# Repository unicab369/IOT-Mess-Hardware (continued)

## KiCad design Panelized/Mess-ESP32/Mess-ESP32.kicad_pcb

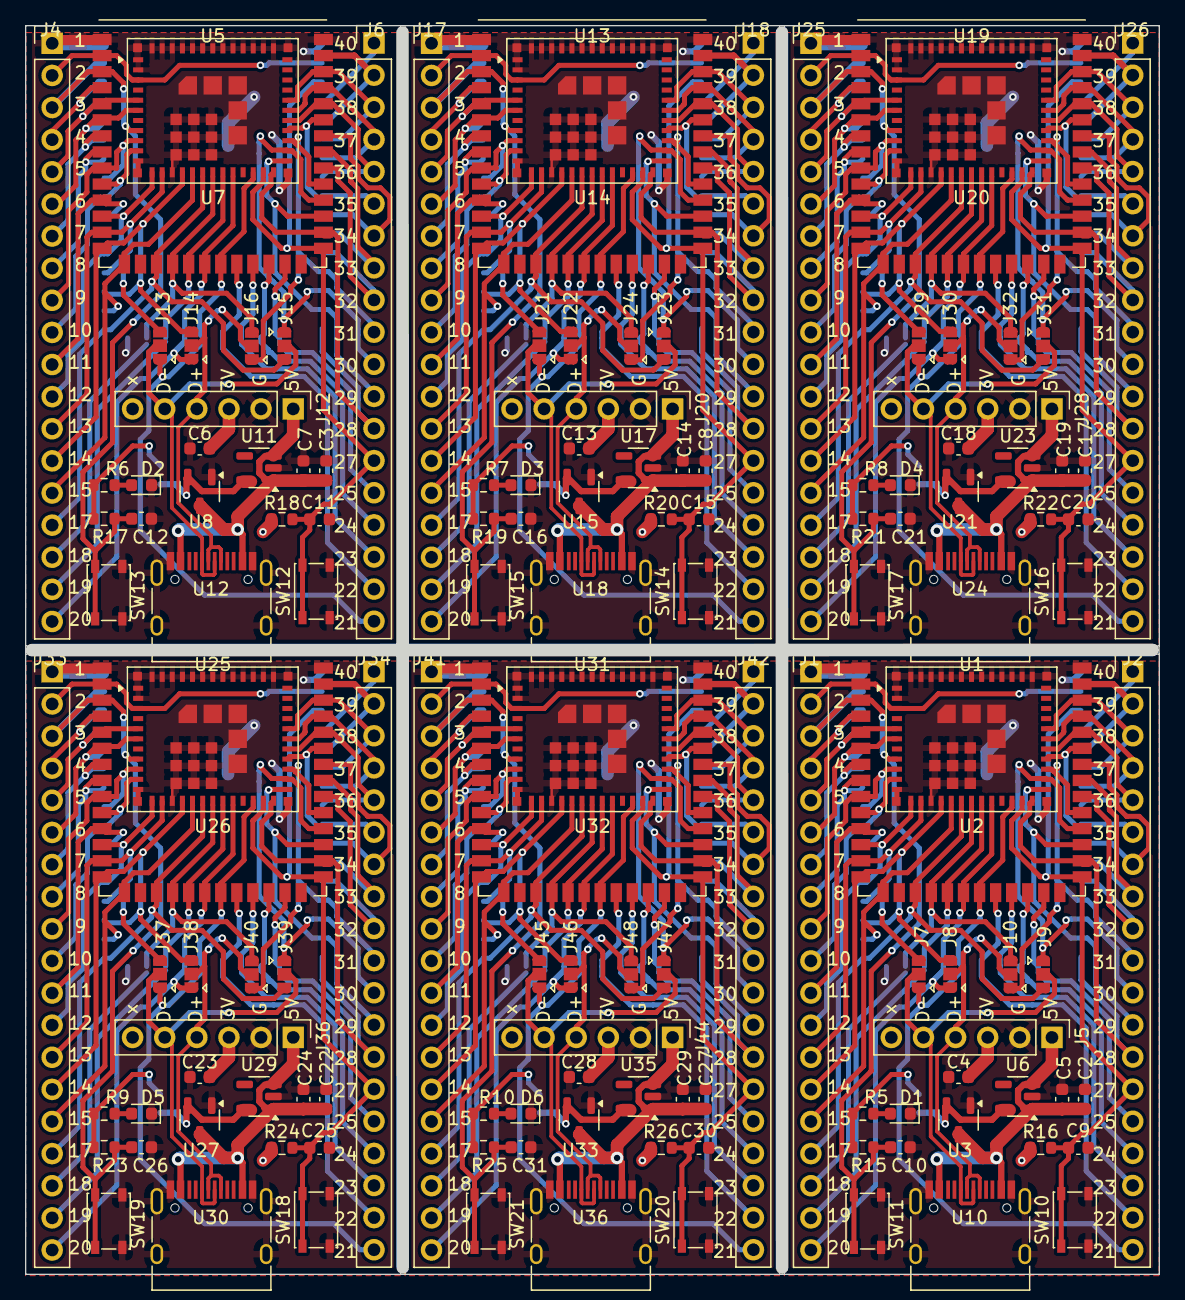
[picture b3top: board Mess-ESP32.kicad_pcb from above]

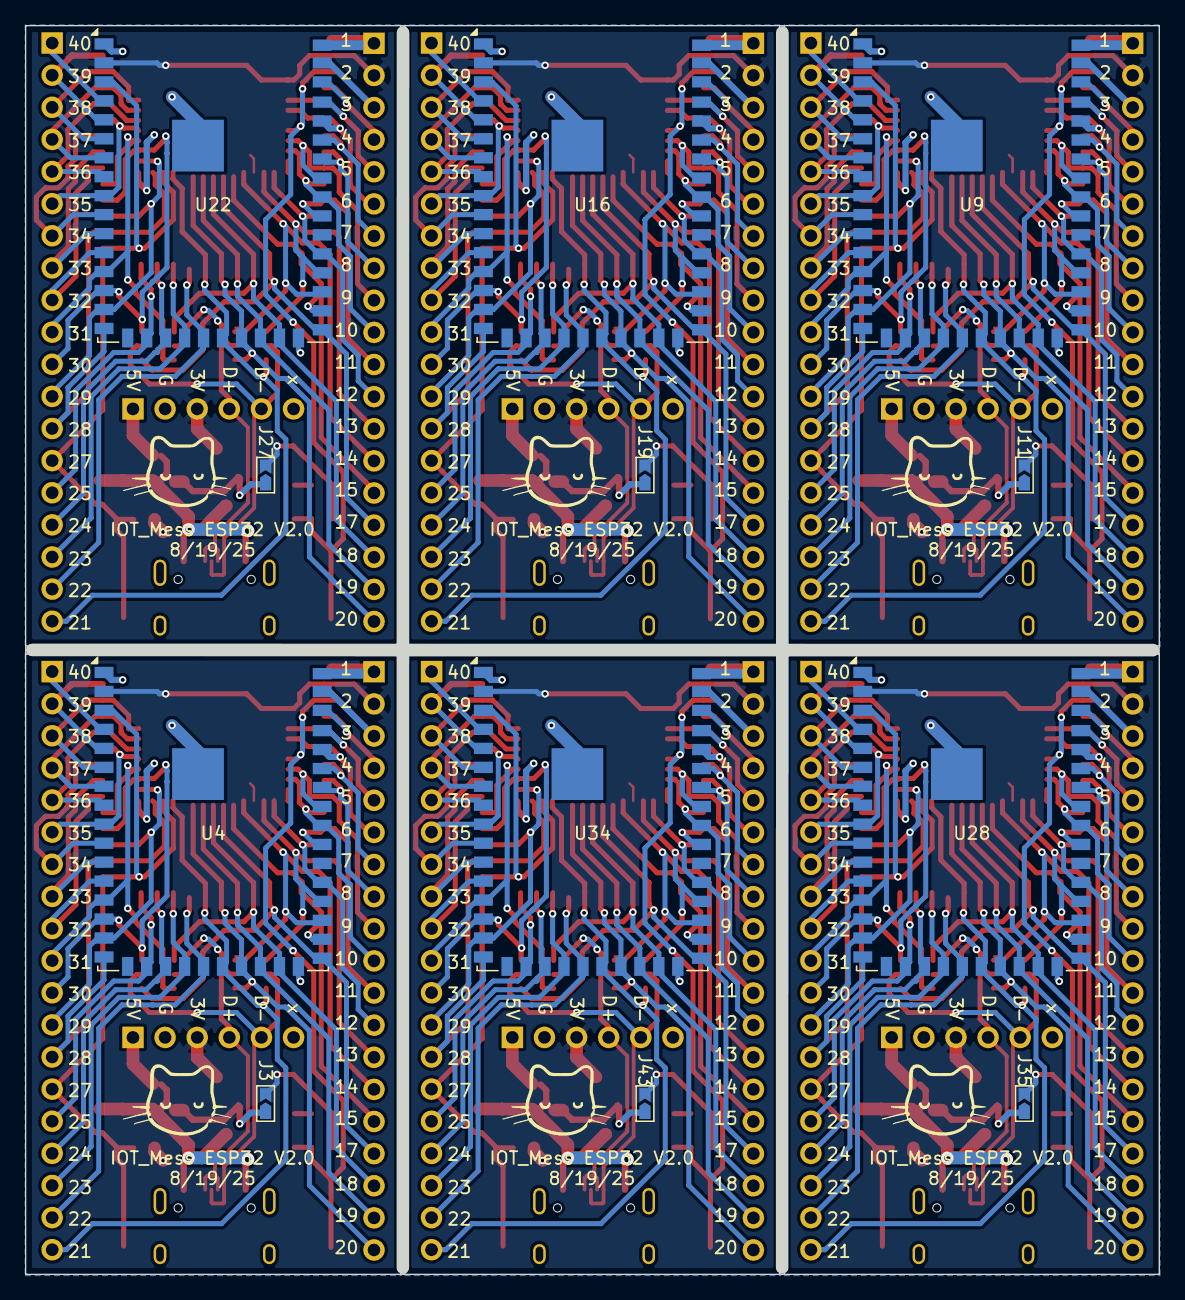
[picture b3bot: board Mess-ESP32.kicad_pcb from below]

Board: 2 copper layers, 89.7 x 98.8 mm, 150 parts (12 on the bottom side), 43 nets.

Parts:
C2, C3, C8, C17, C22, C27: 10u; C_0603_1608Metric
C4, C5, C6, C7, C13, C14, C18, C19, C23, C24, C28, C29: 1u; C_0603_1608Metric
C9, C10, C11, C12, C15, C16, C20, C21, C25, C26, C30, C31: .1u; C_0603_1608Metric
D1, D2, D3, D4, D5, D6: LED; LED_0603_1608Metric
J1, J2, J4, J6, J17, J18, J25, J26, J33, J34, J41, J42: Conn_01x19_Pin; PinHeader_1x19_P2.54mm_Vertical
J3, J11, J19, J27, J35, J43: Jumper_2; Jumpper-triangle
J5, J12, J20, J28, J36, J44: Conn_01x06_Pin; PinHeader_1x06_P2.54mm_Vertical
J7, J8, J9, J10, J13, J14, J15, J16, J21, J22, J23, J24, J29, J30, J31, J32, J37, J38, J39, J40, J45, J46, J47, J48: Jumper; Jumper-3_P1.3mm_Open_RoundedPad1.0x1.5mm
R5, R6, R7, R8, R9, R10: R; R_0603_1608Metric
R15, R16, R17, R18, R19, R20, R21, R22, R23, R24, R25, R26: 10K; R_0603_1608Metric
SW10, SW11, SW12, SW13, SW14, SW15, SW16, SW17, SW18, SW19, SW20, SW21: SW_Push; SW_SPST_PTS810
U1, U5, U13, U19, U25, U31: ESP32-S3-WROOM-1
U2, U7, U14, U20, U26, U32: ESP32-C6-MINI-1
U3, U8, U15, U21, U27, U33: XC6206PxxxMR; SOT-23-3
U4, U9, U16, U22, U28, U34: ESP32-S2-WROVER
U6, U11, U17, U23, U29, U35: ME6211C33M5; SOT-23-5
U10, U12, U18, U24, U30, U36: USB_C_Receptacle_USB2.0_16P; USB_C_Receptacle_HRO_TYPE-C-31-M-12

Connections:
5V: C2.1, C3.1, C5.1, C7.1, C8.1, C14.1, C17.1, C19.1, C22.1, C24.1, C27.1, C29.1, J5.1, J12.1, J20.1, J28.1, J36.1, J44.1, U3.3 (VI), U6.1 (V_{IN}), U6.3 (CE), U8.3 (VI), U10.A4 (VBUS), U10.A9 (VBUS), U10.B4 (VBUS), U10.B9 (VBUS), U11.1 (V_{IN}), U11.3 (CE), U12.A4 (VBUS), U12.A9 (VBUS), U12.B4 (VBUS), U12.B9 (VBUS), U15.3 (VI), U17.1 (V_{IN}), U17.3 (CE), U18.A4 (VBUS), U18.A9 (VBUS), U18.B4 (VBUS), U18.B9 (VBUS), U21.3 (VI), U23.1 (V_{IN}), U23.3 (CE), U24.A4 (VBUS), U24.A9 (VBUS), U24.B4 (VBUS), U24.B9 (VBUS), U27.3 (VI), U29.1 (V_{IN}), U29.3 (CE), U30.A4 (VBUS), U30.A9 (VBUS), U30.B4 (VBUS), U30.B9 (VBUS), U33.3 (VI), U35.1 (V_{IN}), U35.3 (CE), U36.A4 (VBUS), U36.A9 (VBUS), U36.B4 (VBUS), U36.B9 (VBUS)
BOOT: C9.1, C11.1, C15.1, C20.1, C25.1, C30.1, J2.14, J6.14, J18.14, J26.14, J34.14, J42.14, R16.1, R18.1, R20.1, R22.1, R24.1, R26.1, SW10.1, SW12.1, SW14.1, SW16.1, SW18.1, SW20.1, U1.27 (IO9/IO0), U2.23 (IO9), U4.3 (IO00), U5.27 (IO9/IO0), U7.23 (IO9), U9.3 (IO00), U13.27 (IO9/IO0), U14.23 (IO9), U16.3 (IO00), U19.27 (IO9/IO0), U20.23 (IO9), U22.3 (IO00), U25.27 (IO9/IO0), U26.23 (IO9), U28.3 (IO00), U31.27 (IO9/IO0), U32.23 (IO9), U34.3 (IO00)
D+: J5.4, J8.2 (C), J10.2 (C), J12.4, J14.2 (C), J16.2 (C), J20.4, J22.2 (C), J24.2 (C), J28.4, J30.2 (C), J32.2 (C), J36.4, J38.2 (C), J40.2 (C), J44.4, J46.2 (C), J48.2 (C), U10.A6 (D+), U10.B6 (D+), U12.A6 (D+), U12.B6 (D+), U18.A6 (D+), U18.B6 (D+), U24.A6 (D+), U24.B6 (D+), U30.A6 (D+), U30.B6 (D+), U36.A6 (D+), U36.B6 (D+)
D-: J5.5, J7.2 (C), J9.2 (C), J12.5, J13.2 (C), J15.2 (C), J20.5, J21.2 (C), J23.2 (C), J28.5, J29.2 (C), J31.2 (C), J36.5, J37.2 (C), J39.2 (C), J44.5, J45.2 (C), J47.2 (C), U10.A7 (D-), U10.B7 (D-), U12.A7 (D-), U12.B7 (D-), U18.A7 (D-), U18.B7 (D-), U24.A7 (D-), U24.B7 (D-), U30.A7 (D-), U30.B7 (D-), U36.A7 (D-), U36.B7 (D-)
unnamed: D1.2 (A), D2.2 (A), D3.2 (A), D4.2 (A), D5.2 (A), D6.2 (A), R5.2, R6.2, R7.2, R8.2, R9.2, R10.2
unnamed: J3.1 (A), J11.1 (A), J19.1 (A), J27.1 (A), J35.1 (A), J43.1 (A), U3.2 (VO), U6.5 (V_{OUT}), U8.2 (VO), U11.5 (V_{OUT}), U15.2 (VO), U17.5 (V_{OUT}), U21.2 (VO), U23.5 (V_{OUT}), U27.2 (VO), U29.5 (V_{OUT}), U33.2 (VO), U35.5 (V_{OUT})
P1: C2.2, C3.2, C4.2, C5.2, C6.2, C7.2, C8.2, C9.2, C10.2, C11.2, C12.2, C13.2, C14.2, C15.2, C16.2, C17.2, C18.2, C19.2, C20.2, C21.2, C22.2, C23.2, C24.2, C25.2, C26.2, C27.2, C28.2, C29.2, C30.2, C31.2, D1.1 (K), D2.1 (K), D3.1 (K), D4.1 (K), D5.1 (K), D6.1 (K), J1.1, J4.1, J5.2, J12.2, J17.1, J20.2, J25.1, J28.2, J33.1, J36.2, J41.1, J44.2, SW10.2, SW11.2, SW12.2, SW13.2, SW14.2, SW15.2, SW16.2, SW17.2, SW18.2, SW19.2, SW20.2, SW21.2, U1.1 (GND), U1.40 (GND), U1.41 (GND), U2.1 (GND), U2.2 (GND), U2.11 (GND), U2.14 (GND), U2.36 (GND), U2.37 (GND), U2.38 (GND), U2.39 (GND), U2.40 (GND), U2.41 (GND), U2.42 (GND), U2.43 (GND), U2.44 (GND), U2.45 (GND), U2.46 (GND), U2.47 (GND), U2.48 (GND), U2.49 (GND), U2.50 (GND), U2.51 (GND), U2.52 (GND), U2.53 (GND), U3.1 (GND), U4.1 (GND), U4.26 (GND), U4.42 (GND), U4.43 (GND), U5.1 (GND), U5.40 (GND), U5.41 (GND), U6.2 (V_{SS}), U7.1 (GND), U7.2 (GND), U7.11 (GND), U7.14 (GND), U7.36 (GND), U7.37 (GND), U7.38 (GND), U7.39 (GND), U7.40 (GND), U7.41 (GND), U7.42 (GND), U7.43 (GND), U7.44 (GND), U7.45 (GND), U7.46 (GND), U7.47 (GND), U7.48 (GND), U7.49 (GND), U7.50 (GND), U7.51 (GND), U7.52 (GND), U7.53 (GND), U8.1 (GND), U9.1 (GND), U9.26 (GND), U9.42 (GND), U9.43 (GND), U10.A1 (GND), U10.A12 (GND), U10.B1 (GND), U10.B12 (GND), U10.S1 (SHIELD), U11.2 (V_{SS}), U12.A1 (GND), U12.A12 (GND), U12.B1 (GND), U12.B12 (GND), U12.S1 (SHIELD), U13.1 (GND), U13.40 (GND), U13.41 (GND), U14.1 (GND), U14.2 (GND), U14.11 (GND), U14.14 (GND), U14.36 (GND), U14.37 (GND), U14.38 (GND), U14.39 (GND), U14.40 (GND), U14.41 (GND), U14.42 (GND), U14.43 (GND), U14.44 (GND), U14.45 (GND), U14.46 (GND), U14.47 (GND), U14.48 (GND), U14.49 (GND), U14.50 (GND), U14.51 (GND), U14.52 (GND), U14.53 (GND), U15.1 (GND), U16.1 (GND), U16.26 (GND), U16.42 (GND), U16.43 (GND), U17.2 (V_{SS}), U18.A1 (GND), U18.A12 (GND), U18.B1 (GND), U18.B12 (GND), U18.S1 (SHIELD), U19.1 (GND), U19.40 (GND), U19.41 (GND), U20.1 (GND), U20.2 (GND), U20.11 (GND), U20.14 (GND), U20.36 (GND), U20.37 (GND), U20.38 (GND), U20.39 (GND), U20.40 (GND), U20.41 (GND), U20.42 (GND), U20.43 (GND), U20.44 (GND), U20.45 (GND), U20.46 (GND), U20.47 (GND), U20.48 (GND), U20.49 (GND), U20.50 (GND), U20.51 (GND), U20.52 (GND), U20.53 (GND), U21.1 (GND), U22.1 (GND), U22.26 (GND), U22.42 (GND), U22.43 (GND), U23.2 (V_{SS}), U24.A1 (GND), U24.A12 (GND), U24.B1 (GND), U24.B12 (GND), U24.S1 (SHIELD), U25.1 (GND), U25.40 (GND), U25.41 (GND), U26.1 (GND), U26.2 (GND), U26.11 (GND), U26.14 (GND), U26.36 (GND), U26.37 (GND), U26.38 (GND), U26.39 (GND), U26.40 (GND), U26.41 (GND), U26.42 (GND), U26.43 (GND), U26.44 (GND), U26.45 (GND), U26.46 (GND), U26.47 (GND), U26.48 (GND), U26.49 (GND), U26.50 (GND), U26.51 (GND), U26.52 (GND), U26.53 (GND), U27.1 (GND), U28.1 (GND), U28.26 (GND), U28.42 (GND), U28.43 (GND), U29.2 (V_{SS}), U30.A1 (GND), U30.A12 (GND), U30.B1 (GND), U30.B12 (GND), U30.S1 (SHIELD), U31.1 (GND), U31.40 (GND), U31.41 (GND), U32.1 (GND), U32.2 (GND), U32.11 (GND), U32.14 (GND), U32.36 (GND), U32.37 (GND), U32.38 (GND), U32.39 (GND), U32.40 (GND), U32.41 (GND), U32.42 (GND), U32.43 (GND), U32.44 (GND), U32.45 (GND), U32.46 (GND), U32.47 (GND), U32.48 (GND), U32.49 (GND), U32.50 (GND), U32.51 (GND), U32.52 (GND), U32.53 (GND), U33.1 (GND), U34.1 (GND), U34.26 (GND), U34.42 (GND), U34.43 (GND), U35.2 (V_{SS}), U36.A1 (GND), U36.A12 (GND), U36.B1 (GND), U36.B12 (GND), U36.S1 (SHIELD)
P2: C4.1, C6.1, C13.1, C18.1, C23.1, C28.1, J1.2, J3.2 (B), J4.2, J5.3, J11.2 (B), J12.3, J17.2, J19.2 (B), J20.3, J25.2, J27.2 (B), J28.3, J33.2, J35.2 (B), J36.3, J41.2, J43.2 (B), J44.3, R5.1, R6.1, R7.1, R8.1, R9.1, R10.1, R15.2, R16.2, R17.2, R18.2, R19.2, R20.2, R21.2, R22.2, R23.2, R24.2, R25.2, R26.2, U1.2 (3V3), U2.3 (3V3), U4.2 (3V3), U5.2 (3V3), U7.3 (3V3), U9.2 (3V3), U13.2 (3V3), U14.3 (3V3), U16.2 (3V3), U19.2 (3V3), U20.3 (3V3), U22.2 (3V3), U25.2 (3V3), U26.3 (3V3), U28.2 (3V3), U31.2 (3V3), U32.3 (3V3), U34.2 (3V3)
P3: C10.1, C12.1, C16.1, C21.1, C26.1, C31.1, J1.3, J4.3, J17.3, J25.3, J33.3, J41.3, R15.1, R17.1, R19.1, R21.1, R23.1, R25.1, SW11.1, SW13.1, SW15.1, SW17.1, SW19.1, SW21.1, U1.3 (EN), U2.8 (EN), U4.41 (EN), U5.3 (EN), U7.8 (EN), U9.41 (EN), U13.3 (EN), U14.8 (EN), U16.41 (EN), U19.3 (EN), U20.8 (EN), U22.41 (EN), U25.3 (EN), U26.8 (EN), U28.41 (EN), U31.3 (EN), U32.8 (EN), U34.41 (EN)
P4: J1.4, J4.4, J17.4, J25.4, J33.4, J41.4, U1.4 (IO4/IO36*), U4.40 (IO46), U5.4 (IO4/IO36*), U9.40 (IO46), U13.4 (IO4/IO36*), U16.40 (IO46), U19.4 (IO4/IO36*), U22.40 (IO46), U25.4 (IO4/IO36*), U28.40 (IO46), U31.4 (IO4/IO36*), U34.40 (IO46)
P5: J1.5, J4.5, J17.5, J25.5, J33.5, J41.5, U1.5 (IO5/IO39*), U2.5 (IO2), U4.39 (IO45), U5.5 (IO5/IO39*), U7.5 (IO2), U9.39 (IO45), U13.5 (IO5/IO39*), U14.5 (IO2), U16.39 (IO45), U19.5 (IO5/IO39*), U20.5 (IO2), U22.39 (IO45), U25.5 (IO5/IO39*), U26.5 (IO2), U28.39 (IO45), U31.5 (IO5/IO39*), U32.5 (IO2), U34.39 (IO45)
P6: J1.6, J4.6, J17.6, J25.6, J33.6, J41.6, U1.6 (IO6/IO34), U2.6 (IO3), U4.38 (RXD0), U5.6 (IO6/IO34), U7.6 (IO3), U9.38 (RXD0), U13.6 (IO6/IO34), U14.6 (IO3), U16.38 (RXD0), U19.6 (IO6/IO34), U20.6 (IO3), U22.38 (RXD0), U25.6 (IO6/IO34), U26.6 (IO3), U28.38 (RXD0), U31.6 (IO6/IO34), U32.6 (IO3), U34.38 (RXD0)
P7: J1.7, J4.7, J17.7, J25.7, J33.7, J41.7, U1.7 (IO7/IO35), U4.37 (TXD0), U5.7 (IO7/IO35), U9.37 (TXD0), U13.7 (IO7/IO35), U16.37 (TXD0), U19.7 (IO7/IO35), U22.37 (TXD0), U25.7 (IO7/IO35), U28.37 (TXD0), U31.7 (IO7/IO35), U34.37 (TXD0)
P8: J1.8, J4.8, J17.8, J25.8, J33.8, J41.8, U1.8 (IO15/IO32), U4.36 (IO42), U5.8 (IO15/IO32), U9.36 (IO42), U13.8 (IO15/IO32), U16.36 (IO42), U19.8 (IO15/IO32), U22.36 (IO42), U25.8 (IO15/IO32), U28.36 (IO42), U31.8 (IO15/IO32), U34.36 (IO42)
P9: J1.9, J4.9, J17.9, J25.9, J33.9, J41.9, U1.9 (IO16/IO33), U2.9 (IO4), U4.35 (IO41), U5.9 (IO16/IO33), U7.9 (IO4), U9.35 (IO41), U13.9 (IO16/IO33), U14.9 (IO4), U16.35 (IO41), U19.9 (IO16/IO33), U20.9 (IO4), U22.35 (IO41), U25.9 (IO16/IO33), U26.9 (IO4), U28.35 (IO41), U31.9 (IO16/IO33), U32.9 (IO4), U34.35 (IO41)
P10: J1.10, J4.10, J17.10, J25.10, J33.10, J41.10, U1.10 (IO17/IO25), U2.10 (IO5), U4.34 (IO40), U5.10 (IO17/IO25), U7.10 (IO5), U9.34 (IO40), U13.10 (IO17/IO25), U14.10 (IO5), U16.34 (IO40), U19.10 (IO17/IO25), U20.10 (IO5), U22.34 (IO40), U25.10 (IO17/IO25), U26.10 (IO5), U28.34 (IO40), U31.10 (IO17/IO25), U32.10 (IO5), U34.34 (IO40)
P11: J1.11, J4.11, J17.11, J25.11, J33.11, J41.11, U1.11 (IO18/IO26), U4.33 (IO39), U5.11 (IO18/IO26), U9.33 (IO39), U13.11 (IO18/IO26), U16.33 (IO39), U19.11 (IO18/IO26), U22.33 (IO39), U25.11 (IO18/IO26), U28.33 (IO39), U31.11 (IO18/IO26), U34.33 (IO39)
P12: J1.12, J4.12, J17.12, J25.12, J33.12, J41.12, U1.12 (IO19/IO27), U2.12 (IO0), U4.31 (IO37), U5.12 (IO19/IO27), U7.12 (IO0), U9.31 (IO37), U13.12 (IO19/IO27), U14.12 (IO0), U16.31 (IO37), U19.12 (IO19/IO27), U20.12 (IO0), U22.31 (IO37), U25.12 (IO19/IO27), U26.12 (IO0), U28.31 (IO37), U31.12 (IO19/IO27), U32.12 (IO0), U34.31 (IO37)
P13: J1.13, J4.13, J7.3 (B), J13.3 (B), J17.13, J21.3 (B), J25.13, J29.3 (B), J33.13, J37.3 (B), J41.13, J45.3 (B), U1.13 (IO20/IO14), U2.13 (IO1), U4.30 (IO36), U5.13 (IO20/IO14), U7.13 (IO1), U9.30 (IO36), U13.13 (IO20/IO14), U14.13 (IO1), U16.30 (IO36), U19.13 (IO20/IO14), U20.13 (IO1), U22.30 (IO36), U25.13 (IO20/IO14), U26.13 (IO1), U28.30 (IO36), U31.13 (IO20/IO14), U32.13 (IO1), U34.30 (IO36)
P14: J1.14, J4.14, J8.3 (B), J14.3 (B), J17.14, J22.3 (B), J25.14, J30.3 (B), J33.14, J38.3 (B), J41.14, J46.3 (B), U1.14 (IO8/IO12), U2.15 (IO6), U4.29 (IO35), U5.14 (IO8/IO12), U7.15 (IO6), U9.29 (IO35), U13.14 (IO8/IO12), U14.15 (IO6), U16.29 (IO35), U19.14 (IO8/IO12), U20.15 (IO6), U22.29 (IO35), U25.14 (IO8/IO12), U26.15 (IO6), U28.29 (IO35), U31.14 (IO8/IO12), U32.15 (IO6), U34.29 (IO35)
P15: J1.15, J4.15, J17.15, J25.15, J33.15, J41.15, U1.15 (IO3), U2.16 (IO7), U4.28 (IO34), U5.15 (IO3), U7.16 (IO7), U9.28 (IO34), U13.15 (IO3), U14.16 (IO7), U16.28 (IO34), U19.15 (IO3), U20.16 (IO7), U22.28 (IO34), U25.15 (IO3), U26.16 (IO7), U28.28 (IO34), U31.15 (IO3), U32.16 (IO7), U34.28 (IO34)
P17: J1.16, J4.16, J9.3 (B), J15.3 (B), J17.16, J23.3 (B), J25.16, J31.3 (B), J33.16, J39.3 (B), J41.16, J47.3 (B), U1.17 (IO9/IO13), U2.17 (IO12), U4.27 (IO33), U5.17 (IO9/IO13), U7.17 (IO12), U9.27 (IO33), U13.17 (IO9/IO13), U14.17 (IO12), U16.27 (IO33), U19.17 (IO9/IO13), U20.17 (IO12), U22.27 (IO33), U25.17 (IO9/IO13), U26.17 (IO12), U28.27 (IO33), U31.17 (IO9/IO13), U32.17 (IO12), U34.27 (IO33)
P18: J1.17, J4.17, J10.3 (B), J16.3 (B), J17.17, J24.3 (B), J25.17, J32.3 (B), J33.17, J40.3 (B), J41.17, J48.3 (B), U1.18 (IO10), U2.18 (IO13), U4.25 (IO26), U5.18 (IO10), U7.18 (IO13), U9.25 (IO26), U13.18 (IO10), U14.18 (IO13), U16.25 (IO26), U19.18 (IO10), U20.18 (IO13), U22.25 (IO26), U25.18 (IO10), U26.18 (IO13), U28.25 (IO26), U31.18 (IO10), U32.18 (IO13), U34.25 (IO26)
P19: J1.18, J4.18, J17.18, J25.18, J33.18, J41.18, U1.19 (IO11), U2.19 (IO14), U4.24 (IO21), U5.19 (IO11), U7.19 (IO14), U9.24 (IO21), U13.19 (IO11), U14.19 (IO14), U16.24 (IO21), U19.19 (IO11), U20.19 (IO14), U22.24 (IO21), U25.19 (IO11), U26.19 (IO14), U28.24 (IO21), U31.19 (IO11), U32.19 (IO14), U34.24 (IO21)
P20: J1.19, J4.19, J8.1 (A), J14.1 (A), J17.19, J22.1 (A), J25.19, J30.1 (A), J33.19, J38.1 (A), J41.19, J46.1 (A), U1.20 (IO12), U2.20 (IO15), U4.23 (USB_D+), U5.20 (IO12), U7.20 (IO15), U9.23 (USB_D+), U13.20 (IO12), U14.20 (IO15), U16.23 (USB_D+), U19.20 (IO12), U20.20 (IO15), U22.23 (USB_D+), U25.20 (IO12), U26.20 (IO15), U28.23 (USB_D+), U31.20 (IO12), U32.20 (IO15), U34.23 (USB_D+)
P21: J2.19, J6.19, J7.1 (A), J13.1 (A), J18.19, J21.1 (A), J26.19, J29.1 (A), J34.19, J37.1 (A), J42.19, J45.1 (A), U1.21 (IO13), U2.22 (IO8), U4.22 (USB_D-), U5.21 (IO13), U7.22 (IO8), U9.22 (USB_D-), U13.21 (IO13), U14.22 (IO8), U16.22 (USB_D-), U19.21 (IO13), U20.22 (IO8), U22.22 (USB_D-), U25.21 (IO13), U26.22 (IO8), U28.22 (USB_D-), U31.21 (IO13), U32.22 (IO8), U34.22 (USB_D-)
P22: J2.18, J6.18, J18.18, J26.18, J34.18, J42.18, U1.22 (IO14), U4.21 (IO18), U5.22 (IO14), U9.21 (IO18), U13.22 (IO14), U16.21 (IO18), U19.22 (IO14), U22.21 (IO18), U25.22 (IO14), U28.21 (IO18), U31.22 (IO14), U34.21 (IO18)
P23: J2.17, J6.17, J18.17, J26.17, J34.17, J42.17, U1.23 (IO21), U4.20 (IO17), U5.23 (IO21), U9.20 (IO17), U13.23 (IO21), U16.20 (IO17), U19.23 (IO21), U22.20 (IO17), U25.23 (IO21), U28.20 (IO17), U31.23 (IO21), U34.20 (IO17)
P24: J2.16, J6.16, J18.16, J26.16, J34.16, J42.16, U1.24 (IO47/IO15), U4.19 (IO16), U5.24 (IO47/IO15), U9.19 (IO16), U13.24 (IO47/IO15), U16.19 (IO16), U19.24 (IO47/IO15), U22.19 (IO16), U25.24 (IO47/IO15), U28.19 (IO16), U31.24 (IO47/IO15), U34.19 (IO16)
P25: J2.15, J6.15, J18.15, J26.15, J34.15, J42.15, U1.25 (IO48/IO2), U4.18 (IO15), U5.25 (IO48/IO2), U9.18 (IO15), U13.25 (IO48/IO2), U16.18 (IO15), U19.25 (IO48/IO2), U22.18 (IO15), U25.25 (IO48/IO2), U28.18 (IO15), U31.25 (IO48/IO2), U34.18 (IO15)
P28: J2.13, J6.13, J18.13, J26.13, J34.13, J42.13, U1.28 (IO35/IO4), U2.24 (IO18), U4.16 (IO13), U5.28 (IO35/IO4), U7.24 (IO18), U9.16 (IO13), U13.28 (IO35/IO4), U14.24 (IO18), U16.16 (IO13), U19.28 (IO35/IO4), U20.24 (IO18), U22.16 (IO13), U25.28 (IO35/IO4), U26.24 (IO18), U28.16 (IO13), U31.28 (IO35/IO4), U32.24 (IO18), U34.16 (IO13)
P29: J2.12, J6.12, J18.12, J26.12, J34.12, J42.12, U1.29 (IO36/IO16), U2.25 (IO19), U4.15 (IO12), U5.29 (IO36/IO16), U7.25 (IO19), U9.15 (IO12), U13.29 (IO36/IO16), U14.25 (IO19), U16.15 (IO12), U19.29 (IO36/IO16), U20.25 (IO19), U22.15 (IO12), U25.29 (IO36/IO16), U26.25 (IO19), U28.15 (IO12), U31.29 (IO36/IO16), U32.25 (IO19), U34.15 (IO12)
P30: J2.11, J6.11, J9.1 (A), J15.1 (A), J18.11, J23.1 (A), J26.11, J31.1 (A), J34.11, J39.1 (A), J42.11, J47.1 (A), U1.30 (IO37/IO17), U2.26 (IO20), U4.14 (IO11), U5.30 (IO37/IO17), U7.26 (IO20), U9.14 (IO11), U13.30 (IO37/IO17), U14.26 (IO20), U16.14 (IO11), U19.30 (IO37/IO17), U20.26 (IO20), U22.14 (IO11), U25.30 (IO37/IO17), U26.26 (IO20), U28.14 (IO11), U31.30 (IO37/IO17), U32.26 (IO20), U34.14 (IO11)
P31: J2.10, J6.10, J10.1 (A), J16.1 (A), J18.10, J24.1 (A), J26.10, J32.1 (A), J34.10, J40.1 (A), J42.10, J48.1 (A), U1.31 (IO38/IO5), U2.27 (IO21), U4.13 (IO10), U5.31 (IO38/IO5), U7.27 (IO21), U9.13 (IO10), U13.31 (IO38/IO5), U14.27 (IO21), U16.13 (IO10), U19.31 (IO38/IO5), U20.27 (IO21), U22.13 (IO10), U25.31 (IO38/IO5), U26.27 (IO21), U28.13 (IO10), U31.31 (IO38/IO5), U32.27 (IO21), U34.13 (IO10)
P32: J2.9, J6.9, J18.9, J26.9, J34.9, J42.9, U1.32 (IO39/IO18), U4.12 (IO09), U5.32 (IO39/IO18), U9.12 (IO09), U13.32 (IO39/IO18), U16.12 (IO09), U19.32 (IO39/IO18), U22.12 (IO09), U25.32 (IO39/IO18), U28.12 (IO09), U31.32 (IO39/IO18), U34.12 (IO09)
P33: J2.8, J6.8, J18.8, J26.8, J34.8, J42.8, U1.33 (IO40/IO19), U4.11 (IO08), U5.33 (IO40/IO19), U9.11 (IO08), U13.33 (IO40/IO19), U16.11 (IO08), U19.33 (IO40/IO19), U22.11 (IO08), U25.33 (IO40/IO19), U28.11 (IO08), U31.33 (IO40/IO19), U34.11 (IO08)
P34: J2.7, J6.7, J18.7, J26.7, J34.7, J42.7, U1.34 (IO41/NC), U4.10 (IO07), U5.34 (IO41/NC), U9.10 (IO07), U13.34 (IO41/NC), U16.10 (IO07), U19.34 (IO41/NC), U22.10 (IO07), U25.34 (IO41/NC), U28.10 (IO07), U31.34 (IO41/NC), U34.10 (IO07)
P35: J2.6, J6.6, J18.6, J26.6, J34.6, J42.6, U1.35 (IO42/IO21), U2.28 (IO22), U4.9 (IO06), U5.35 (IO42/IO21), U7.28 (IO22), U9.9 (IO06), U13.35 (IO42/IO21), U14.28 (IO22), U16.9 (IO06), U19.35 (IO42/IO21), U20.28 (IO22), U22.9 (IO06), U25.35 (IO42/IO21), U26.28 (IO22), U28.9 (IO06), U31.35 (IO42/IO21), U32.28 (IO22), U34.9 (IO06)
P36: J2.5, J6.5, J18.5, J26.5, J34.5, J42.5, U1.36 (RX0), U2.29 (IO23), U4.8 (IO05), U5.36 (RX0), U7.29 (IO23), U9.8 (IO05), U13.36 (RX0), U14.29 (IO23), U16.8 (IO05), U19.36 (RX0), U20.29 (IO23), U22.8 (IO05), U25.36 (RX0), U26.29 (IO23), U28.8 (IO05), U31.36 (RX0), U32.29 (IO23), U34.8 (IO05)
P37: J2.4, J6.4, J18.4, J26.4, J34.4, J42.4, U1.37 (TX0), U2.30 (RXD0), U4.7 (IO04), U5.37 (TX0), U7.30 (RXD0), U9.7 (IO04), U13.37 (TX0), U14.30 (RXD0), U16.7 (IO04), U19.37 (TX0), U20.30 (RXD0), U22.7 (IO04), U25.37 (TX0), U26.30 (RXD0), U28.7 (IO04), U31.37 (TX0), U32.30 (RXD0), U34.7 (IO04)
P38: J2.3, J6.3, J18.3, J26.3, J34.3, J42.3, U1.38 (IO2/IO22), U2.31 (TXD0), U4.6 (IO03), U5.38 (IO2/IO22), U7.31 (TXD0), U9.6 (IO03), U13.38 (IO2/IO22), U14.31 (TXD0), U16.6 (IO03), U19.38 (IO2/IO22), U20.31 (TXD0), U22.6 (IO03), U25.38 (IO2/IO22), U26.31 (TXD0), U28.6 (IO03), U31.38 (IO2/IO22), U32.31 (TXD0), U34.6 (IO03)
P39: J2.2, J6.2, J18.2, J26.2, J34.2, J42.2, U1.39 (IO1/IO23), U4.5 (IO02), U5.39 (IO1/IO23), U9.5 (IO02), U13.39 (IO1/IO23), U16.5 (IO02), U19.39 (IO1/IO23), U22.5 (IO02), U25.39 (IO1/IO23), U28.5 (IO02), U31.39 (IO1/IO23), U34.5 (IO02)
P40: J2.1, J6.1, J18.1, J26.1, J34.1, J42.1, U4.4 (IO01), U9.4 (IO01), U16.4 (IO01), U22.4 (IO01), U28.4 (IO01), U34.4 (IO01)
